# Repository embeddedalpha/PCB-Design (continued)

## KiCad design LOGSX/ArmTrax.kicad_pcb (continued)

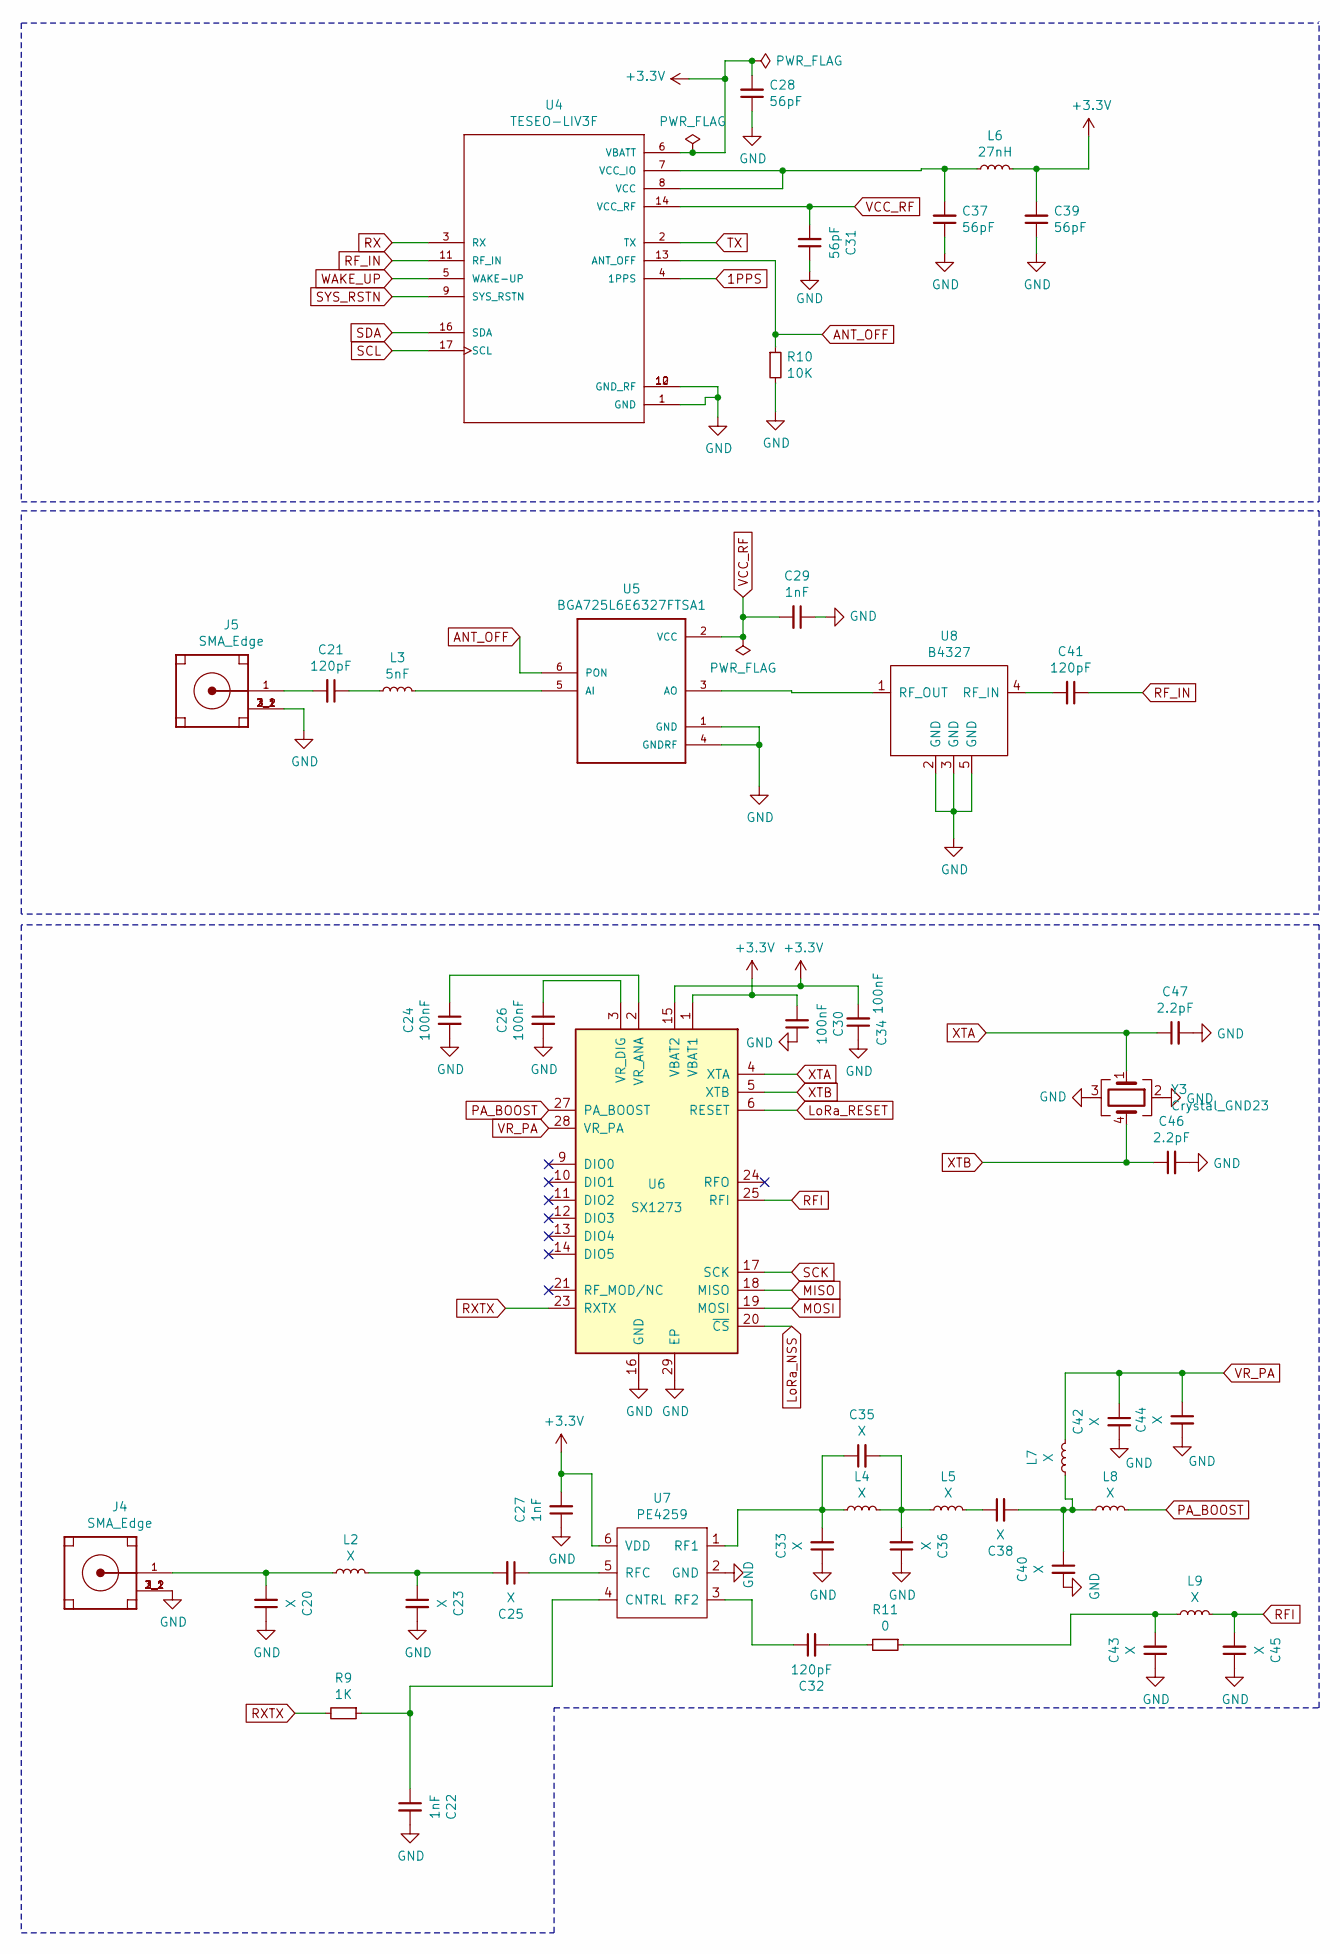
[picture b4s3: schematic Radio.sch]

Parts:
C20, C23, C25, C33, C35, C36, C38, C40, C42, C43, C44, C45: X; C_0201_0603Metric
C21, C32, C41: 120pF; C_0201_0603Metric
C22, C27, C29: 1nF; C_0201_0603Metric
C24, C26, C30, C34: 100nF; C_0201_0603Metric
C28, C31, C37, C39: 56pF; C_0201_0603Metric
C46, C47: 2.2pF; C_0201_0603Metric
J4, J5: SMA_Edge; SMA-J-P-H-ST-EM1
L2, L4, L5, L7, L8, L9: X; L_0201_0603Metric
L3: 5nF; L_0201_0603Metric
L6: 27nH; L_0201_0603Metric
R9: 1K; R_0402_1005Metric
R10: 10K; R_0402_1005Metric
R11: 0; R_0402_1005Metric
U4: TESEO-LIV3F
U5: BGA725L6E6327FTSA1
U6: SX1273; QFN-28-1EP_6x6mm_P0.65mm_EP4.8x4.8mm
U7: PE4259; PE4259_sc70
U8: B4327
Y3: Crystal_GND23; Crystal_SMD_Abracon_ABM8G-4Pin_3.2x2.5mm

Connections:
1PPS: U4.4 (1PPS); also elsewhere on the board
ANT_OFF: R10.1, U4.13 (ANT_OFF), U5.6 (PON)
LoRa_NSS: U6.20 (~CS~); also elsewhere on the board
LoRa_RESET: U6.6 (RESET); also elsewhere on the board
MISO: U6.18 (MISO); also elsewhere on the board
MOSI: U6.19 (MOSI); also elsewhere on the board
unnamed: C20.2, J4.1 (SIGNAL), L2.1
unnamed: C21.1, L3.1
unnamed: C21.2, J5.1 (SIGNAL)
unnamed: C22.1, R9.1, U7.4 (CNTRL)
unnamed: C23.1, C25.2, L2.2
unnamed: C24.1, U6.2 (VR_ANA)
unnamed: C25.1, U7.5 (RFC)
unnamed: C26.1, U6.3 (VR_DIG)
unnamed: C32.1, U7.3 (RF2)
unnamed: C32.2, R11.2
unnamed: C33.2, C35.1, L4.1, U7.1 (RF1)
unnamed: C35.2, C36.2, L4.2, L5.1
unnamed: C37.2, L6.1, U4.7 (VCC_IO), U4.8 (VCC)
unnamed: C38.1, L5.2
unnamed: C38.2, C40.1, L7.1, L8.1
unnamed: C41.2, U8.4 (RF_IN)
unnamed: C43.2, L9.1, R11.1
unnamed: L3.2, U5.5 (AI)
unnamed: U5.3 (AO), U8.1 (RF_OUT)
PA_BOOST: L8.2, U6.27 (PA_BOOST)
RFI: C45.2, L9.2, U6.25 (RFI)
RF_IN: C41.1, U4.11 (RF_IN)
RX: U4.3 (RX); also elsewhere on the board
RXTX: R9.2, U6.23 (RXTX)
SCK: U6.17 (SCK); also elsewhere on the board
SCL: U4.17 (SCL); also elsewhere on the board
SDA: U4.16 (SDA); also elsewhere on the board
TX: U4.2 (TX); also elsewhere on the board
VCC_RF: C29.2, C31.2, U4.14 (VCC_RF), U5.2 (VCC)
VR_PA: C42.1, C44.1, L7.2, U6.28 (VR_PA)
WAKE_UP: U4.5 (WAKE-UP); also elsewhere on the board
XTA: C47.1, U6.4 (XTA), Y3.1
XTB: C46.1, U6.5 (XTB), Y3.4

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
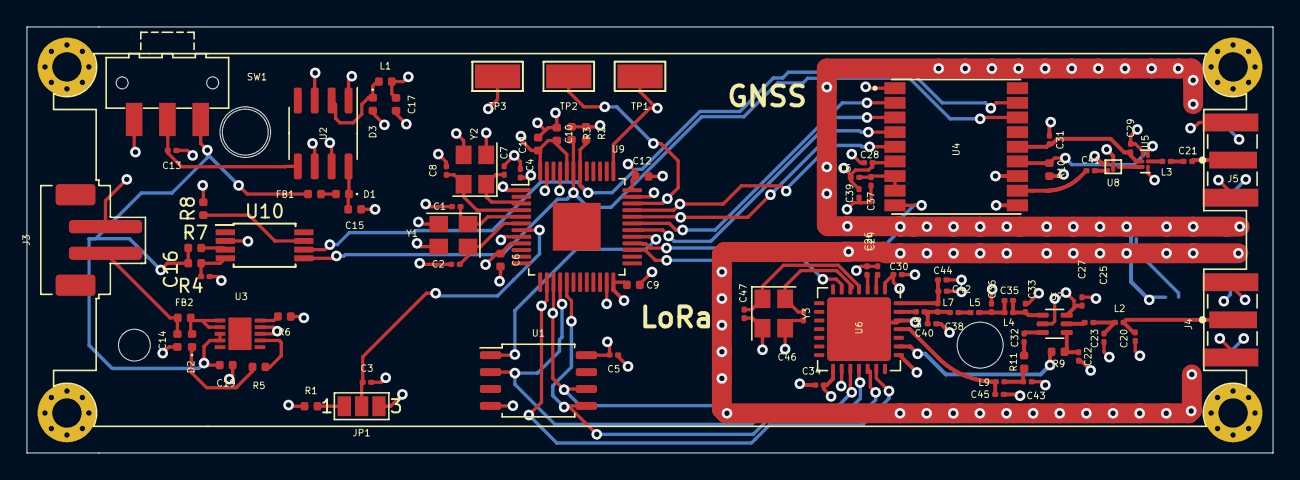
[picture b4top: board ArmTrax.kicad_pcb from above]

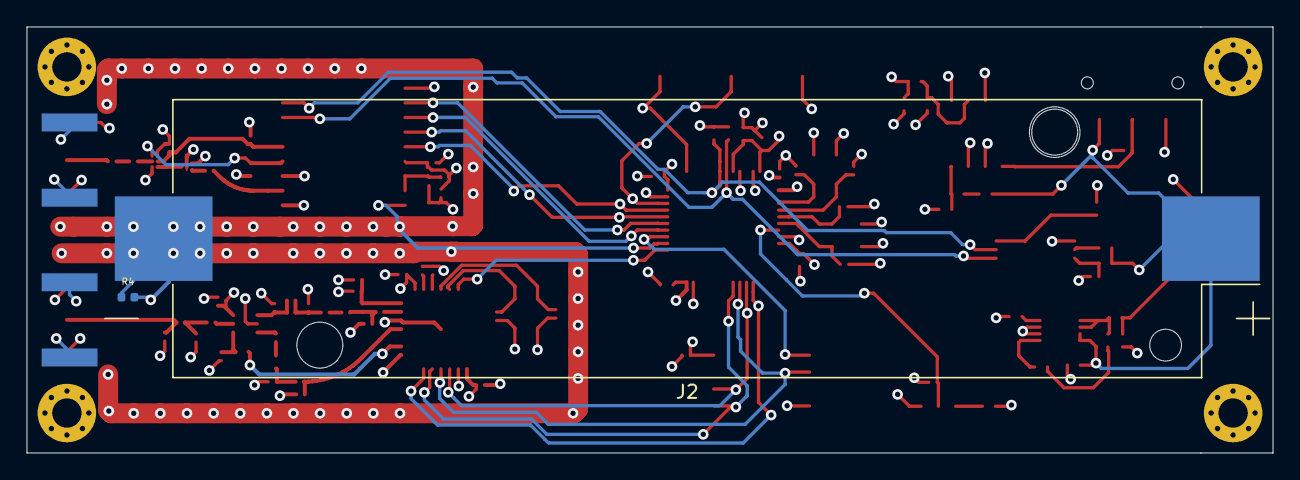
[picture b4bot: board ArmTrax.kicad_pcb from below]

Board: 4 copper layers, 93.6 x 32.0 mm, 94 parts (2 on the bottom side), 63 nets.

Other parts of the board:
R4#2: R_Small; R_0402_1005Metric
U9: STM32F103C8Tx; LQFP-48-1EP_7x7mm_P0.5mm_EP3.6x3.6mm

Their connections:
1PPS: U9.32; also elsewhere on the board
FLASH_NSS: U9.29; also elsewhere on the board
LoRa_NSS: U9.14; also elsewhere on the board
LoRa_RESET: U9.27; also elsewhere on the board
MISO: U9.16; also elsewhere on the board
MOSI: U9.17; also elsewhere on the board
unnamed 9: U9.7; also elsewhere on the board
OSC32_IN: U9.3; also elsewhere on the board
OSC32_OUT: U9.4; also elsewhere on the board
OSC_IN: U9.5; also elsewhere on the board
OSC_OUT: U9.6; also elsewhere on the board
RX: U9.30; also elsewhere on the board
SCK: U9.15; also elsewhere on the board
SCL: U9.42; also elsewhere on the board
SDA: U9.43; also elsewhere on the board
SWCLK: U9.37; also elsewhere on the board
SWDIO: U9.34; also elsewhere on the board
TX: U9.31; also elsewhere on the board
WAKE_UP: U9.33; also elsewhere on the board

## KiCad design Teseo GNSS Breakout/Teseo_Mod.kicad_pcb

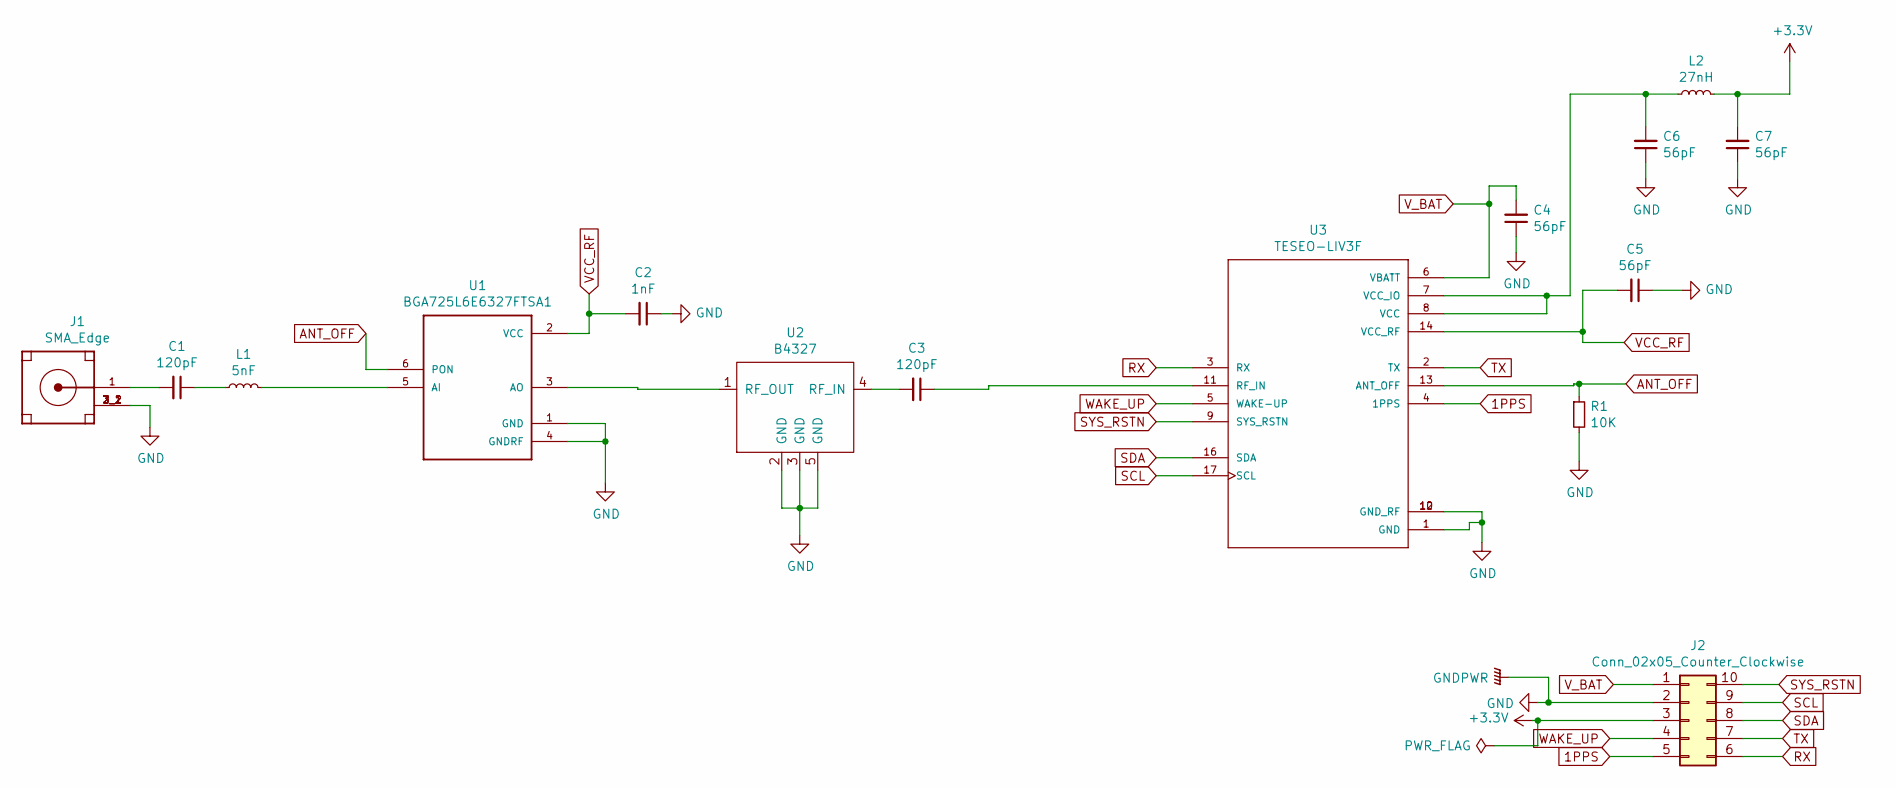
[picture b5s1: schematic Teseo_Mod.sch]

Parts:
C1, C3: 120pF; C_0201_0603Metric
C2: 1nF; C_0201_0603Metric
C4, C5, C6, C7: 56pF; C_0201_0603Metric
J1: SMA_Edge; SMA-J-P-H-ST-EM1
J2: Conn_02x05_Counter_Clockwise; PinHeader_2x05_P2.54mm_Horizontal
L1: 5nF; L_0201_0603Metric
L2: 27nH; L_0201_0603Metric
R1: 10K; L_0201_0603Metric
U1: BGA725L6E6327FTSA1
U2: B4327
U3: TESEO-LIV3F

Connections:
1PPS: J2.5, U3.4 (1PPS)
+3V3: C7.2, J2.3, L2.2
ANT_OFF: R1.1, U1.6 (PON), U3.13 (ANT_OFF)
GND: C2.1, C4.1, C5.1, C6.1, C7.1, J1.2_1 (GND), J1.2_2 (GND), J1.3_1 (GND), J1.3_2 (GND), J2.2, R1.2, U1.1 (GND), U1.4 (GNDRF), U2.2 (GND), U2.3 (GND), U2.5 (GND), U3.1 (GND), U3.10 (GND_RF), U3.12 (GND_RF)
unnamed: C1.1, L1.1
unnamed: C1.2, J1.1 (SIGNAL)
unnamed: C3.1, U3.11 (RF_IN)
unnamed: C3.2, U2.4 (RF_IN)
unnamed: C6.2, L2.1, U3.7 (VCC_IO), U3.8 (VCC)
unnamed: L1.2, U1.5 (AI)
unnamed: U1.3 (AO), U2.1 (RF_OUT)
RX: J2.6, U3.3 (RX)
SCL: J2.9, U3.17 (SCL)
SDA: J2.8, U3.16 (SDA)
SYS_RSTN: J2.10, U3.9 (SYS_RSTN)
TX: J2.7, U3.2 (TX)
VCC_RF: C2.2, C5.2, U1.2 (VCC), U3.14 (VCC_RF)
V_BAT: C4.2, J2.1, U3.6 (VBATT)
WAKE_UP: J2.4, U3.5 (WAKE-UP)

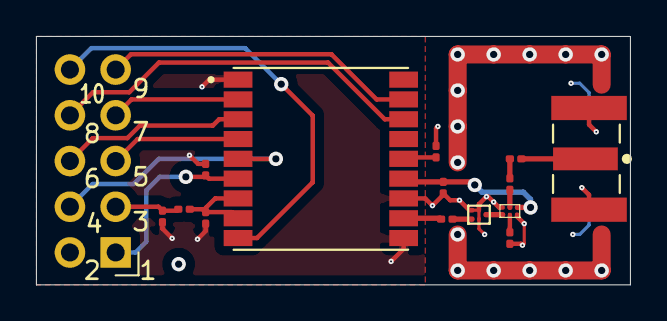
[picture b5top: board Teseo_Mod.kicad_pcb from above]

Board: 4 copper layers, 33.0 x 13.8 mm, 15 parts (0 on the bottom side), 19 nets.

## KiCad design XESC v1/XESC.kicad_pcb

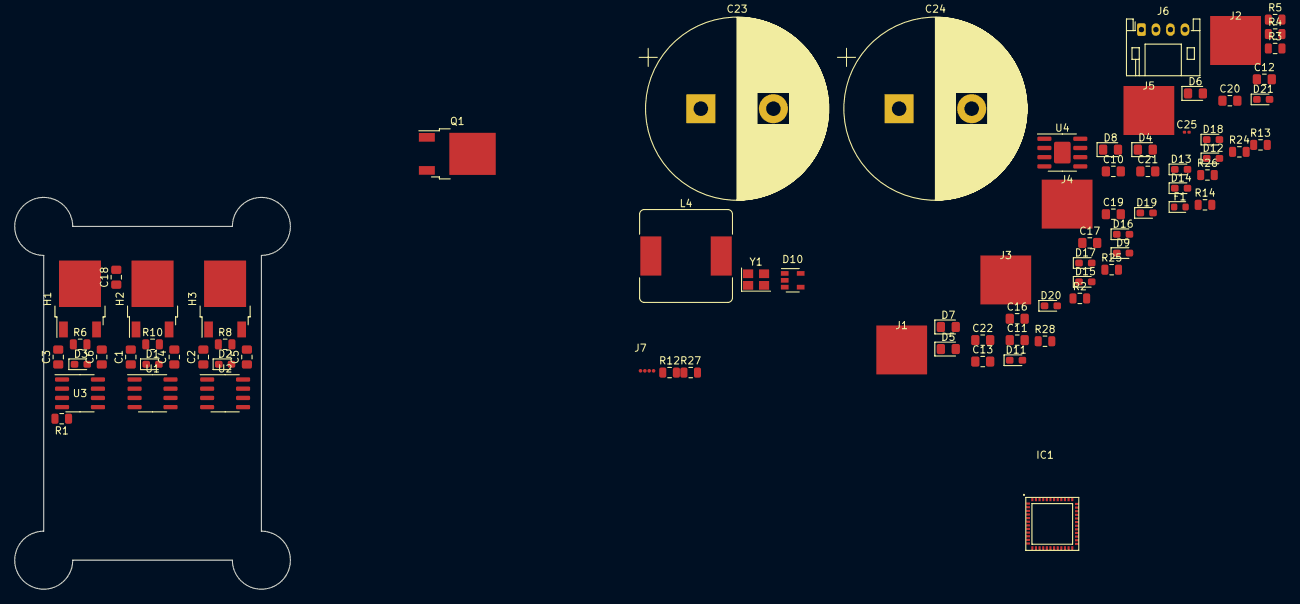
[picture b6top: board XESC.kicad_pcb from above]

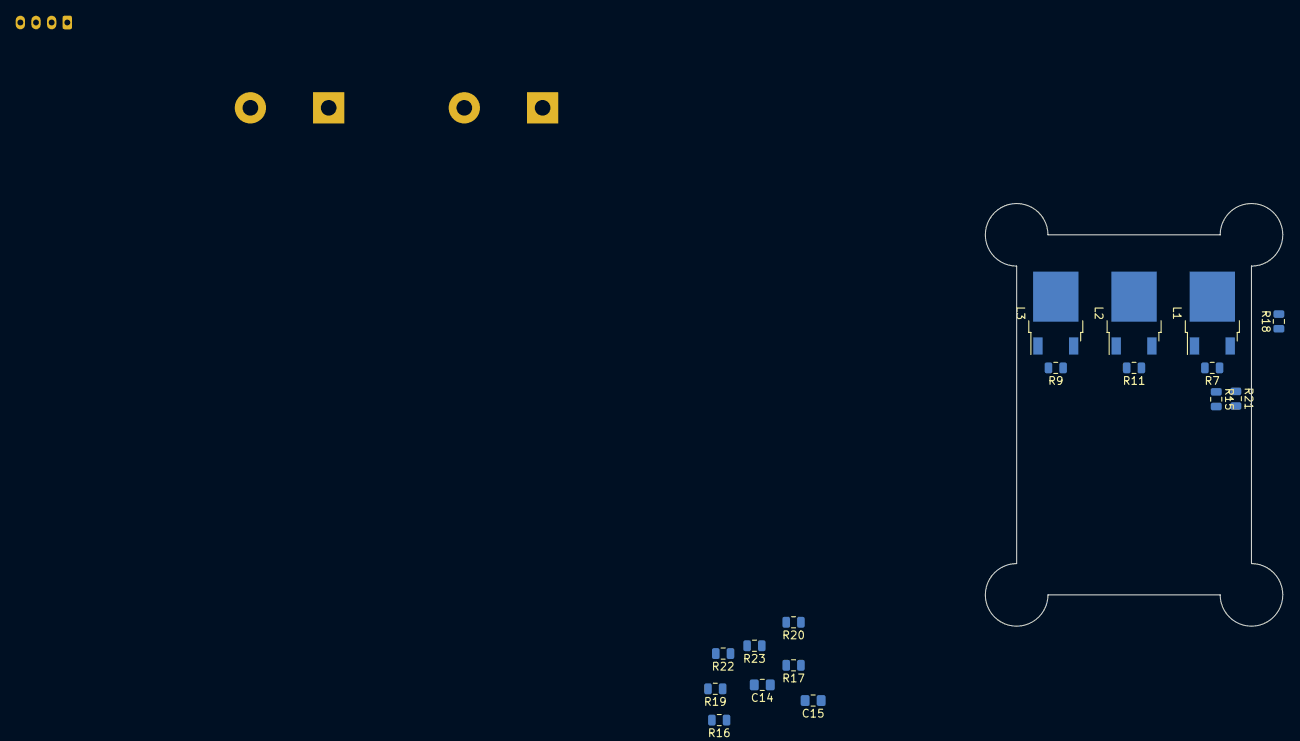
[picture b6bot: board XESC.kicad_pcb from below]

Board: 2 copper layers, 38.0 x 54.0 mm, 93 parts (17 on the bottom side), 60 nets, no tracks yet.

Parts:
C1, C2, C3, C10, C11, C12, C13, C16, C17, C19, C20, C21, C22: 100N; C_0805_2012Metric_Pad1.15x1.40mm_HandSolder
C4, C5, C6: 4.7U; C_0805_2012Metric_Pad1.15x1.40mm_HandSolder
C14, C15, C18: 1U; C_0805_2012Metric_Pad1.15x1.40mm_HandSolder
C23, C24: 100N; CP_Radial_D25.0mm_P10.00mm_SnapIn
C25: C_Small; C_0201_0603Metric
D1, D2, D3, D11, D20, D21: DIODE; D_0603_1608Metric_Pad1.05x0.95mm_HandSolder
D4: POWER_ON_LED; LED_0805_2012Metric_Pad1.15x1.40mm_HandSolder
D5: INDC_LED; LED_0805_2012Metric_Pad1.15x1.40mm_HandSolder
D6: RED_LED; LED_0805_2012Metric_Pad1.15x1.40mm_HandSolder
D7: BLUE_LED; LED_0805_2012Metric_Pad1.15x1.40mm_HandSolder
D8: GREEN_LED; LED_0805_2012Metric_Pad1.15x1.40mm_HandSolder
D9: D_Zener_Small; D_0603_1608Metric_Pad1.05x0.95mm_HandSolder
D10: SP0504BAHT; SOT-23-5
D12, D13, D14, D15, D16, D17, D18, D19: D_TVS; D_0603_1608Metric_Pad1.05x0.95mm_HandSolder
F1: Fuse; D_0603_1608Metric
H1, H2, H3: IRFR3504ZPbF; TO-252-2
IC1: STM32G473CEU6; STM32G47CEU6x
J1, J2, J3: PHASE A; PAD_7X6.75
J4: PWR_IN; PAD_7X6.75
J5: GND; PAD_7X6.75
J6: UART; JST_PH_S4B-PH-K_1x04_P2.00mm_Horizontal
J7: SWD; SWD_PINS
L1, L2, L3: IRFR3504ZPbF; TO-252-2
L4: L_Small; L_Bourns_SRR1260
Q1: QM6015D; TO-252-2
R1, R2, R3, R24: 10K; R_0805_2012Metric
R4, R5, R12, R13, R14, R26: 1K; R_0805_2012Metric
R6, R7, R8, R9, R10, R11, R15, R16, R17, R18, R19, R20, R21, R22, R23, R27, R28: 100; R_0805_2012Metric
R25: R_Small; R_0805_2012Metric
U1, U2, U3: IR2101; SOIC-8_3.9x4.9mm_P1.27mm
U4: ADP2302ARDZ-3.3; SOIC-8-1EP_3.9x4.9mm_P1.27mm_EP2.29x3mm
Y1: 20MHz; Crystal_SMD_SeikoEpson_FA238-4Pin_3.2x2.5mm

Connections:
CON_A: H1.3, J3.1, L1.2
CON_B: C4.2, H2.3, J1.1, L2.2, U1.6
CON_C: C5.2, H3.3, J2.1, L3.2, U2.6
EN: IC1.33, U4.3
H1: R6.2, U3.7
H2: R10.2, U1.7
H3: R8.2, U2.7
INDC_LED: D5.2, IC1.12
L1: R7.2, U3.5
L2: R11.2, U1.5
L3: R9.2, U2.5
LED_BLUE: D7.2, IC1.17
LED_GREEN: D8.2, IC1.16
LED_RED: D6.2, IC1.13
unnamed: C4.1, D1.2, U1.8
unnamed: C5.1, D2.2, U2.8
unnamed: C6.1, D3.2, U3.8
unnamed: C18.1, R15.1, R18.2, R21.2
unnamed: C25.1, D11.2, L4.1, U4.8
unnamed: C25.2, U4.1
unnamed: D4.1, R4.2
unnamed: D5.1, R5.2
unnamed: D6.1, R12.1
unnamed: D7.1, R13.1
unnamed: D8.1, R14.1
unnamed: D9.1, Q1.3, U4.2
unnamed: D9.2, Q1.1, R25.1
unnamed: D10.1, D12.1, D20.1, J6.1
unnamed: D13.1, D21.1, J7.1
unnamed: F1.1, Q1.2
unnamed: H1.1, R6.1
unnamed: H2.1, R10.1
unnamed: H3.1, R8.1
unnamed: IC1.7, R24.2
unnamed: IC1.45, R26.2
unnamed: L1.1, R7.1
unnamed: L2.1, R11.1
unnamed: L3.1, R9.1
unnamed: R16.1, R19.2, R22.2
unnamed: R17.1, R20.2, R23.2
unnamed: R27.1, R28.2, U4.5
OSC_IN: C12.1, IC1.5, Y1.1
OSC_OUT: C13.1, IC1.6, Y1.4
PHASE_A__ADC: IC1.25, R15.2
PHASE_B__ADC: C14.1, IC1.26, R16.2
PHASE_C__ADC: C15.1, IC1.27, R17.2
PWR_ON: C10.2, C11.2, C16.2, C17.2, C19.2, C20.2, C21.2, C22.2, D4.2, D20.2, D21.2, IC1.20, IC1.21, IC1.24, IC1.36, IC1.48, L4.2, R24.1, R27.2
SIG_H_1: IC1.8, U3.2
SIG_H_2: IC1.10, U1.2
SIG_H_3: IC1.14, U2.2
SIG_L_1: IC1.9, R1.2, U3.3
SIG_L_2: IC1.11, R2.2, U1.3
SIG_L_3: IC1.15, R3.2, U2.3
SWCLK: D15.1, IC1.37, J7.2
SWDIO: D17.1, IC1.38, J7.3
UART_RX: D10.4, D16.1, IC1.32, J6.3
UART_TX: D10.3, D14.1, IC1.31, J6.2
V1: C6.2, U3.6
VDD: C1.1, C2.1, C3.1, C23.1, C24.1, D1.1, D2.1, D3.1, F1.2, H1.2, H2.2, H3.2, J4.1, U1.1, U2.1, U3.1
VSSA: C1.2, C2.2, C3.2, C10.1, C11.1, C12.2, C13.2, C14.2, C15.2, C16.1, C17.1, C18.2, C19.1, C20.1, C21.1, C22.1, C23.2, C24.2, D10.2, D10.5, D11.1, D12.2, D13.2, D14.2, D15.2, D16.2, D17.2, D18.1, D18.2, D19.1, D19.2, IC1.19, IC1.23, IC1.35, IC1.47, J5.1, J6.4, J7.4, L1.3, L2.3, L3.3, R1.1, R2.1, R3.1, R4.1, R5.1, R12.2, R13.2, R14.2, R18.1, R19.1, R20.1, R25.2, R26.1, R28.1, U1.4, U2.4, U3.4, U4.7, U4.9, Y1.2, Y1.3

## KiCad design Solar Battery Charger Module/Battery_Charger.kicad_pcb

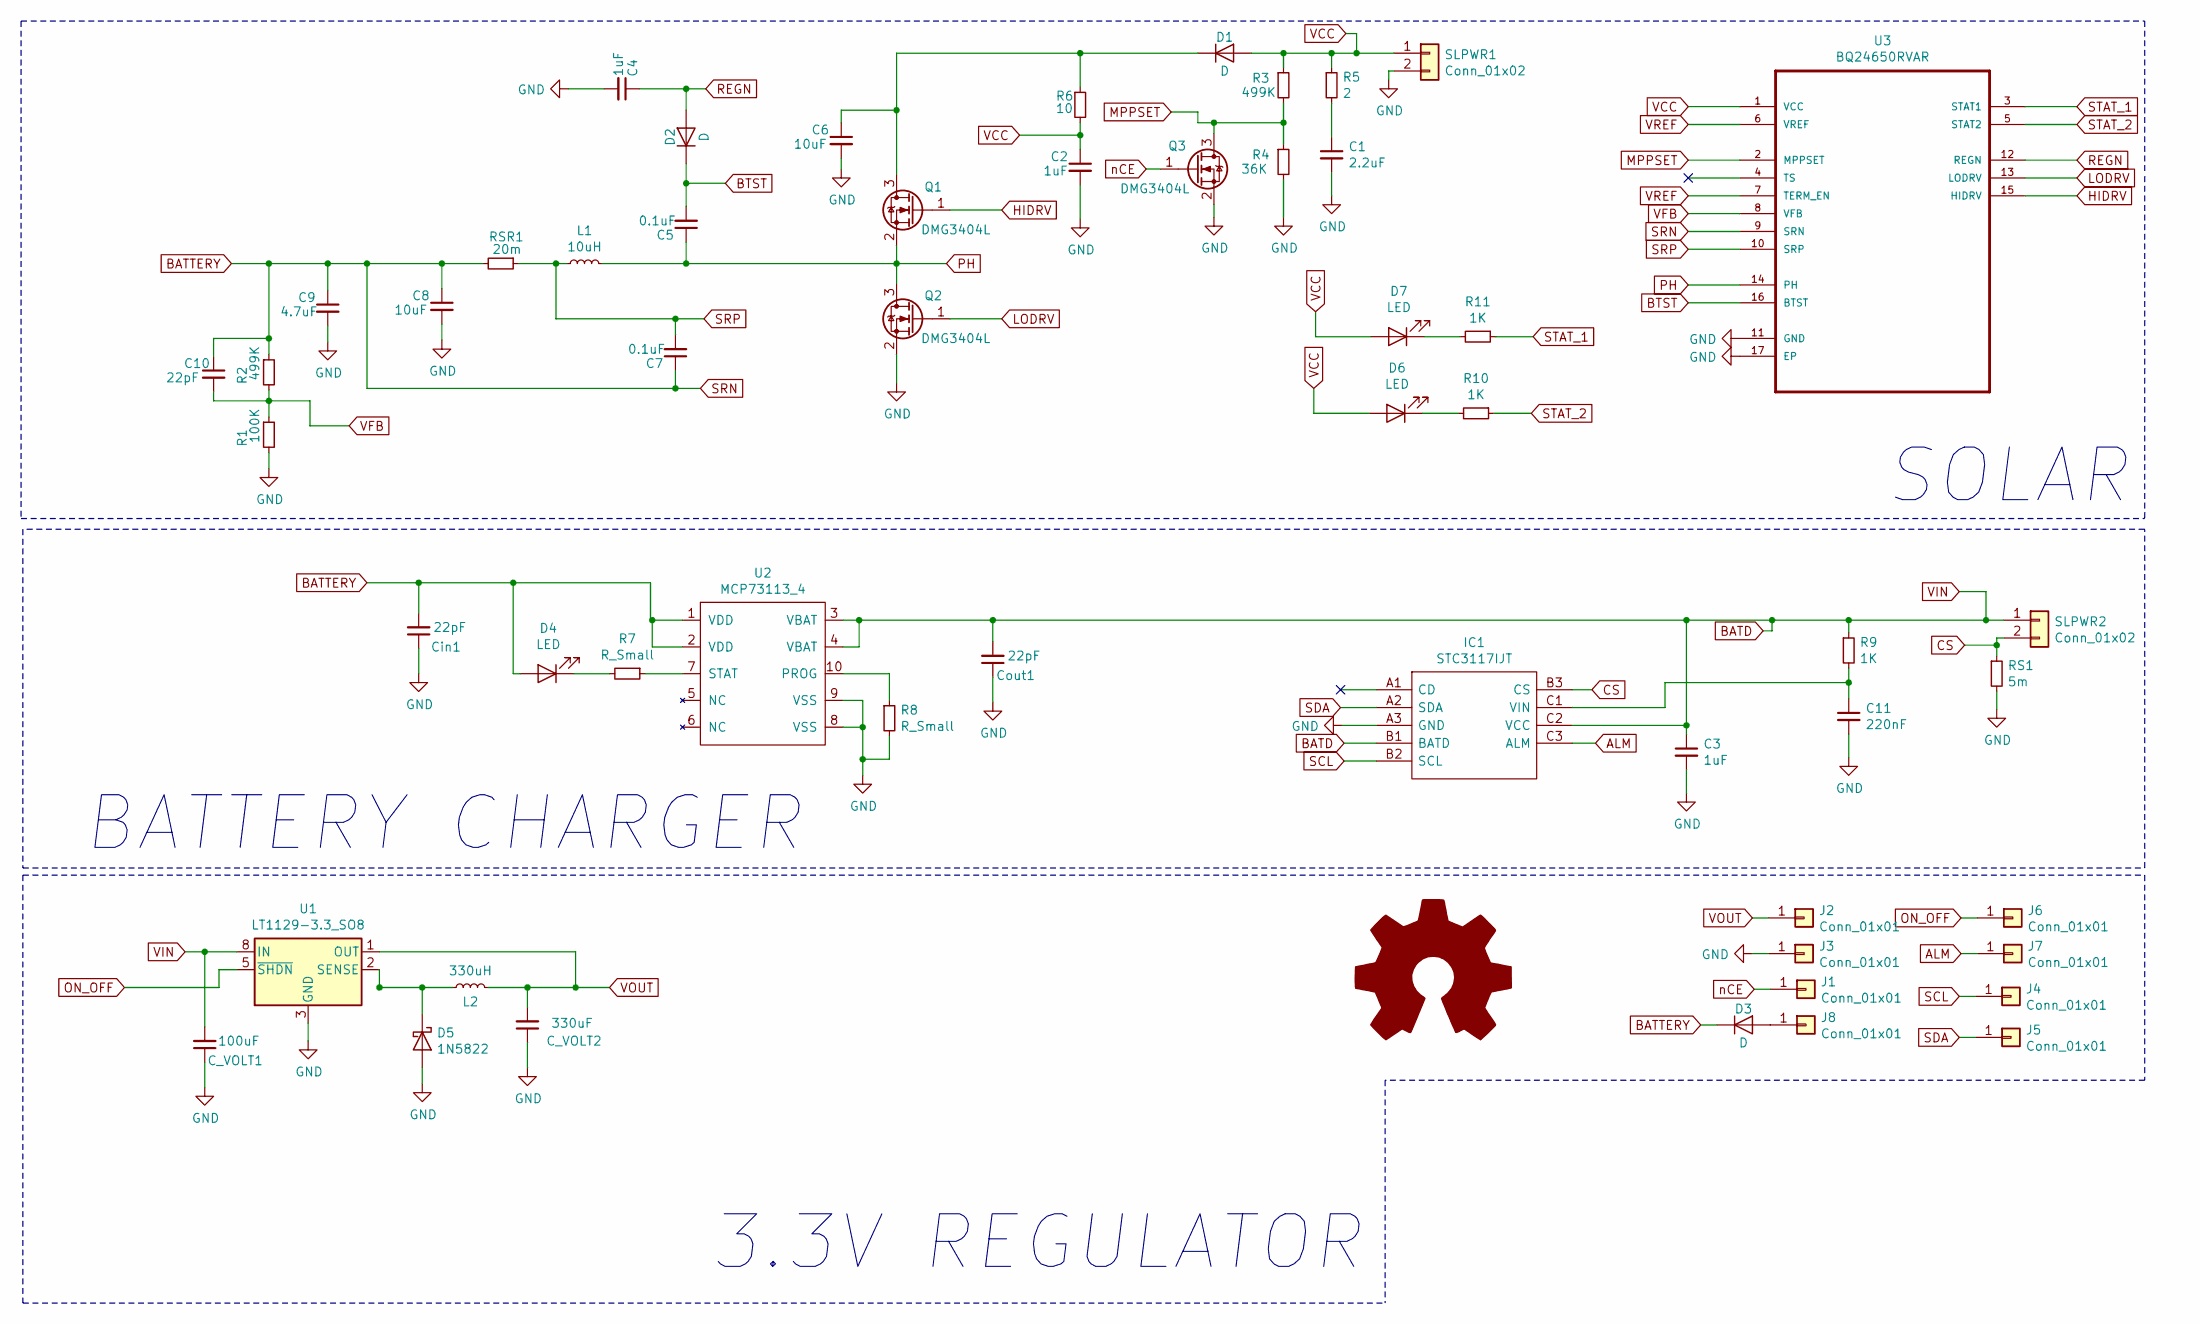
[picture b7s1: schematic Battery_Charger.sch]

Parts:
C1: 2.2uF; C_0201_0603Metric
C2, C3, C4: 1uF; C_0201_0603Metric
C5, C7: 0.1uF; C_0201_0603Metric
C6, C8: 10uF; C_0201_0603Metric
C9: 4.7uF; C_0201_0603Metric
C10: 22pF; C_0201_0603Metric
C11: 220nF; C_0201_0603Metric
C_VOLT1: 100uF; C_0201_0603Metric
C_VOLT2: 330uF; C_0201_0603Metric
Cin1: 22pF; C_0201_0603Metric
Cout1: 22pF; C_0201_0603Metric
D1, D2, D3: D; D_0201_0603Metric
D4, D6, D7: LED; LED_0201_0603Metric
D5: 1N5822; D_0201_0603Metric
IC1: STC3117IJT; BGA9C40P3X3_146X156X66; Mouser Part Number 511-STC3117IJT
J1, J2, J3, J4, J5, J6, J7, J8: Conn_01x01; Module_Footprint
L1: 10uH; L_0201_0603Metric
L2: 330uH; L_0201_0603Metric
Q1, Q2, Q3: DMG3404L; SOT-23
R1: 100K; R_0201_0603Metric
R2, R3: 499K; R_0201_0603Metric
R4: 36K; R_0201_0603Metric
R5: 2; R_0201_0603Metric
R6: 10; R_0201_0603Metric
R7, R8: R_Small; R_0201_0603Metric
R9, R10, R11: 1K; R_0201_0603Metric
RS1: 5m; R_0201_0603Metric
RSR1: 20m; R_0201_0603Metric
SLPWR1, SLPWR2: Conn_01x02; JST_PH_B2B-PH-SM4-TB_1x02-1MP_P2.00mm_Vertical
U1: LT1129-3.3_SO8; SOIC-8_3.9x4.9mm_P1.27mm
U2: MCP73113_4; MCP73113
U3: BQ24650RVAR; QFN50P350X350X100-17N

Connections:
ALM: IC1.C3 (ALM), J7.1
BATD: C3.1, C_VOLT1.2, Cout1.2, IC1.B1 (BATD), IC1.C2 (VCC), R9.1, SLPWR2.1, U1.8 (IN), U2.3 (VBAT), U2.4 (VBAT)
BATTERY: C7.1, C8.1, C9.1, C10.1, Cin1.2, D3.1 (K), D4.2 (A), R2.1, RSR1.2, U2.1 (VDD), U2.2 (VDD), U3.9 (SRN)
BTST: C5.2, D2.1 (K), U3.16 (BTST)
CS: IC1.B3 (CS), RS1.1, SLPWR2.2
GND: C1.2, C2.2, C3.2, C4.2, C6.2, C8.2, C9.2, C11.2, C_VOLT1.1, C_VOLT2.1, Cin1.1, Cout1.1, D5.2 (A), IC1.A3 (GND), J3.1, Q2.2 (S), Q3.2 (S), R1.2, R4.2, R8.2, RS1.2, SLPWR1.2, U1.3 (GND), U1.6 (GND), U1.7 (GND), U2.8 (VSS), U2.9 (VSS), U3.11 (GND), U3.17 (EP)
HIDRV: Q1.1 (G), U3.15 (HIDRV)
LODRV: Q2.1 (G), U3.13 (LODRV)
MPPSET: Q3.3 (D), R3.2, R4.1, U3.2 (MPPSET)
unnamed: C1.1, R5.2
unnamed: C6.1, D1.1 (K), Q1.3 (D), R6.1
unnamed: C11.1, IC1.C1 (VIN), R9.2
unnamed: D3.2 (A), J8.1
unnamed: D4.1 (K), R7.2
unnamed: D5.1 (K), L2.1, U1.2 (SENSE), U1.4 (NC)
unnamed: D6.1 (K), R10.2
unnamed: D7.1 (K), R11.2
unnamed: R7.1, U2.7 (STAT)
unnamed: R8.1, U2.10 (PROG)
ON_OFF: J6.1, U1.5 (~SHDN)
PH: C5.1, L1.2, Q1.2 (S), Q2.3 (D), U3.14 (PH)
REGN: C4.1, D2.2 (A), U3.12 (REGN)
SCL: IC1.B2 (SCL), J4.1
SDA: IC1.A2 (SDA), J5.1
SRP: C7.2, L1.1, RSR1.1, U3.10 (SRP)
STAT_1: R11.1, U3.3 (STAT1)
STAT_2: R10.1, U3.5 (STAT2)
VCC: C2.1, D1.2 (A), D6.2 (A), D7.2 (A), R3.1, R5.1, R6.2, SLPWR1.1, U3.1 (VCC)
VFB: C10.2, R1.1, R2.2, U3.8 (VFB)
VOUT: C_VOLT2.2, J2.1, L2.2, U1.1 (OUT)
VREF: U3.6 (VREF), U3.7 (TERM_EN)
nCE: J1.1, Q3.1 (G)

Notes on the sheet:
SOLAR
BATTERY CHARGER
3.3V REGULATOR

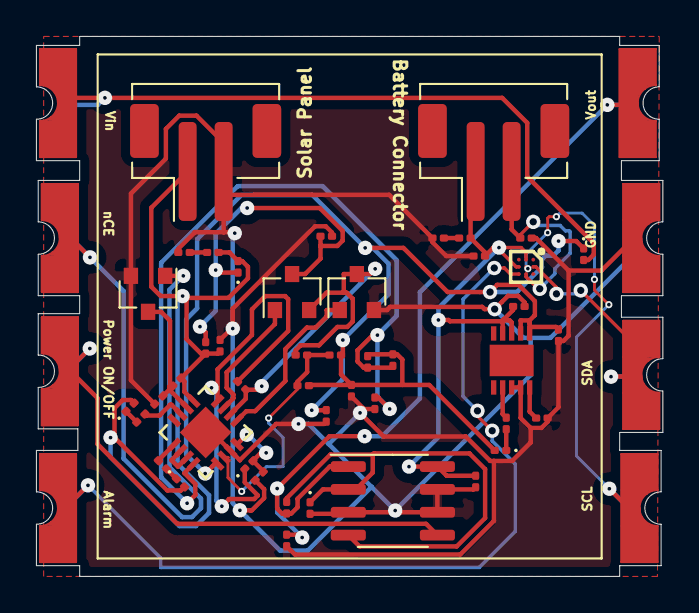
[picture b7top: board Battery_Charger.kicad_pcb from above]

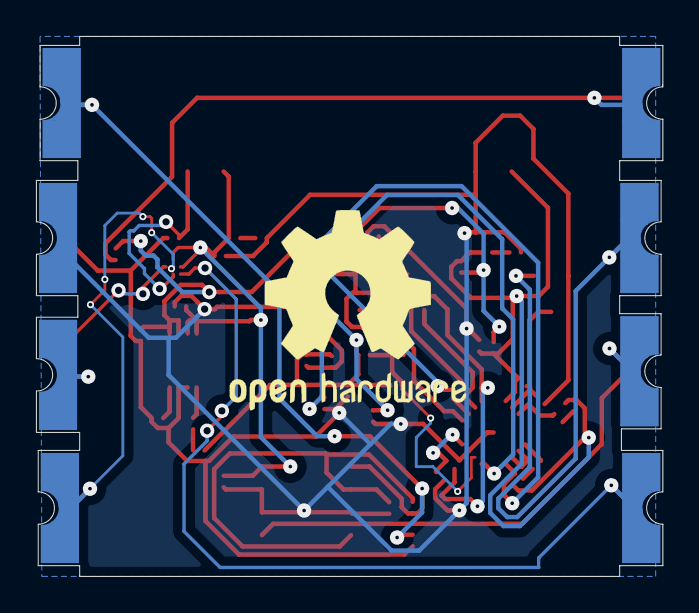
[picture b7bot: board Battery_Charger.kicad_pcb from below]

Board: 2 copper layers, 34.8 x 30.0 mm, 54 parts (2 on the bottom side), 32 nets.

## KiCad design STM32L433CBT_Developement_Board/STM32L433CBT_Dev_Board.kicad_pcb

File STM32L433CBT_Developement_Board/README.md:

<h1> STM32L433CBTx Development Board </h1>

<h3>More views</h3>

<br>

<br>

<h3> Front Copper</h3>

<br>

<h3> Back Copper</h3>

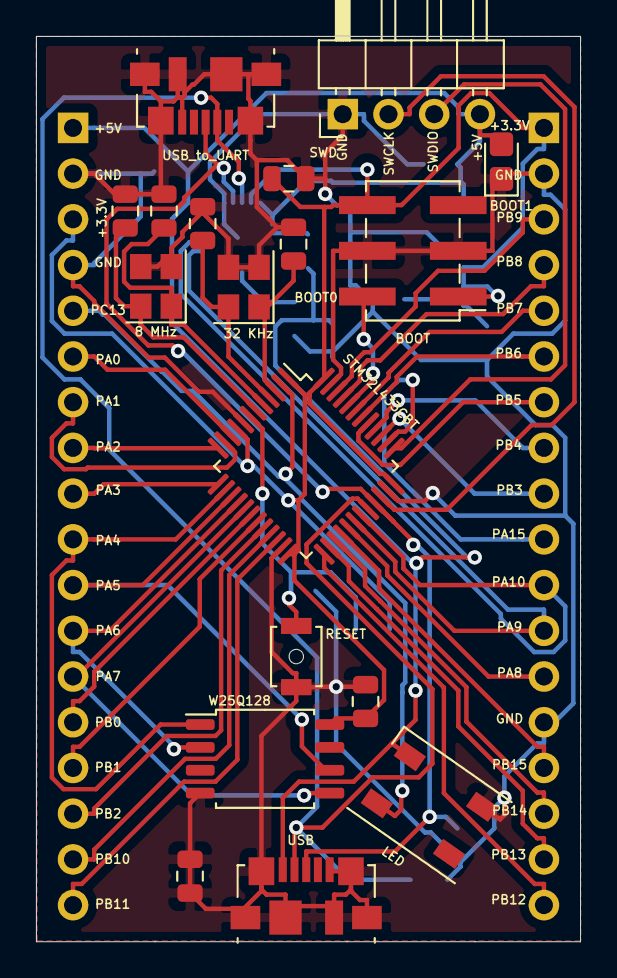
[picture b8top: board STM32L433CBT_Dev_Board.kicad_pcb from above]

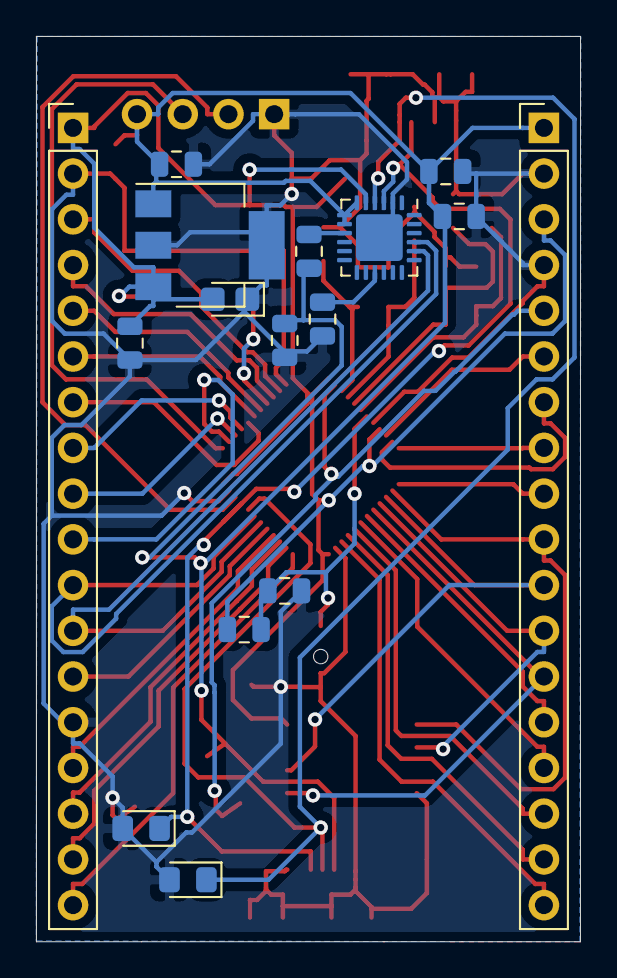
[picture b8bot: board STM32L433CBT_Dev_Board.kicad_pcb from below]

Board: 2 copper layers, 30.2 x 50.3 mm, 34 parts (16 on the bottom side), 44 nets.

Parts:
BOOT: Conn_02x03_Counter_Clockwise; PinHeader_2x03_P2.54mm_Vertical_SMD
C1, C2, C3, C4, C5, C6, C8, C9, C10, C11, C12, C13, C14: C_Small; C_0805_2012Metric
D7, D9: D_TVS; D_0805_2012Metric_Pad1.15x1.40mm_HandSolder
D10, D12: LED; LED_0805_2012Metric_Castellated
J2, J3: Conn_01x18_Male; PinHeader_1x18_P2.54mm_Vertical
J7: USB_B_Micro; USB_Micro-B_Molex_47346-0001
LED: NeoPixel_THT; LED_WS2812B_PLCC4_5.0x5.0mm_P3.2mm
R1, R2, R3: R_Small; R_0805_2012Metric
RESET: SW_DIP_x01; SW_SPST_B3U-1000P-B
STM32L433CBT: STM32L433CBTx; LQFP-48_7x7mm_P0.5mm
SWD: Conn_01x04_Male; PinHeader_1x04_P2.54mm_Horizontal
U2: CP2102N-A01-GQFN24; QFN-24-1EP_4x4mm_P0.5mm_EP2.6x2.6mm
U4: LT1963AxST-3.3; SOT-223-3_TabPin2
USB_to_UART: USB_B_Micro; USB_Micro-B_Molex_47346-0001
W25Q128: W25Q128JVS; SOIC-8_5.23x5.23mm_P1.27mm
Y1, Y2: Crystal_GND23_Small; Crystal_SMD_Abracon_ABM8G-4Pin_3.2x2.5mm

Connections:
+3V3: BOOT.1, BOOT.6, C4.2, C6.1, C8.1, D12.2, J2.1, J3.3, R3.1, STM32L433CBT.1, STM32L433CBT.9, STM32L433CBT.24, STM32L433CBT.36, STM32L433CBT.48, U2.5, U4.3, W25Q128.8
+5V: C1.1, C2.2, C3.1, C5.1, D10.2, J3.1, J7.1, LED.3, R1.2, SWD.4, U2.6, U2.7, U2.8, U4.1
/BOOT0: BOOT.2, STM32L433CBT.44
/D+: D9.1, J7.3, STM32L433CBT.33, U2.3, USB_to_UART.3
/D-: D7.1, J7.2, STM32L433CBT.32, U2.4, USB_to_UART.2
/NRST: C13.2, R3.2, RESET.1, STM32L433CBT.7
/OSC8_IN: C10.1, STM32L433CBT.5, Y2.1
/OSC8_OUT: C9.1, STM32L433CBT.6, Y2.4
/OSC32_IN: C12.1, STM32L433CBT.3, Y1.1
/OSC32_OUT: C11.1, STM32L433CBT.4, Y1.4
/PA0: J3.6, STM32L433CBT.10
/PA1: J3.7, STM32L433CBT.11
/PA2: J3.8, STM32L433CBT.12
/PA3: J3.9, STM32L433CBT.13
/PA4: J3.10, STM32L433CBT.14, W25Q128.1
/PA5: J3.11, STM32L433CBT.15, W25Q128.6
/PA6: J3.12, STM32L433CBT.16, W25Q128.2
/PA7: J3.13, STM32L433CBT.17, W25Q128.5
/PA8: J2.13, STM32L433CBT.29
/PA9: J2.12, STM32L433CBT.30, U2.20
/PA10: J2.11, STM32L433CBT.31, U2.21
/PA13: STM32L433CBT.34, SWD.2
/PA14: STM32L433CBT.37, SWD.3
/PA15: J2.10, STM32L433CBT.38
/PB0: J3.14, STM32L433CBT.18
/PB1: J3.15, STM32L433CBT.19
/PB2: J3.16, STM32L433CBT.20
/PB3: J2.9, STM32L433CBT.39
/PB4: J2.8, STM32L433CBT.40
/PB5: J2.7, STM32L433CBT.41
/PB6: J2.6, STM32L433CBT.42
/PB7: J2.5, STM32L433CBT.43
/PB8: J2.4, STM32L433CBT.45
/PB9: J2.3, STM32L433CBT.46
/PB10: J3.17, STM32L433CBT.21
/PB11: J3.18, STM32L433CBT.22
/PB12: J2.18, STM32L433CBT.25
/PB13: J2.17, STM32L433CBT.26
/PB14: J2.16, STM32L433CBT.27
/PB15: J2.15, STM32L433CBT.28
/PC13: J3.5, LED.4, STM32L433CBT.2
GND: BOOT.3, BOOT.4, C1.2, C2.1, C3.2, C4.1, C5.2, C6.2, C8.2, C9.2, C10.2, C11.2, C12.2, C13.1, C14.1, C14.2, D7.2, D9.2, D10.1, D12.1, J2.2, J2.14, J3.2, J3.4, J7.5, J7.6, LED.2, R2.2, RESET.2, STM32L433CBT.8, STM32L433CBT.23, STM32L433CBT.35, STM32L433CBT.47, SWD.1, U2.2, U2.25, U4.2, USB_to_UART.5, USB_to_UART.6, W25Q128.4, Y1.2, Y1.3, Y2.2, Y2.3
unnamed: R1.1, U2.9
unnamed: R2.1, U2.15

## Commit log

2020-03-19 Create txt
2020-04-17 Create SNAPS
2020-05-16 Create t
